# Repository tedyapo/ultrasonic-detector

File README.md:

# ultrasonic-detector
Digital down-converting ultrasonic detector

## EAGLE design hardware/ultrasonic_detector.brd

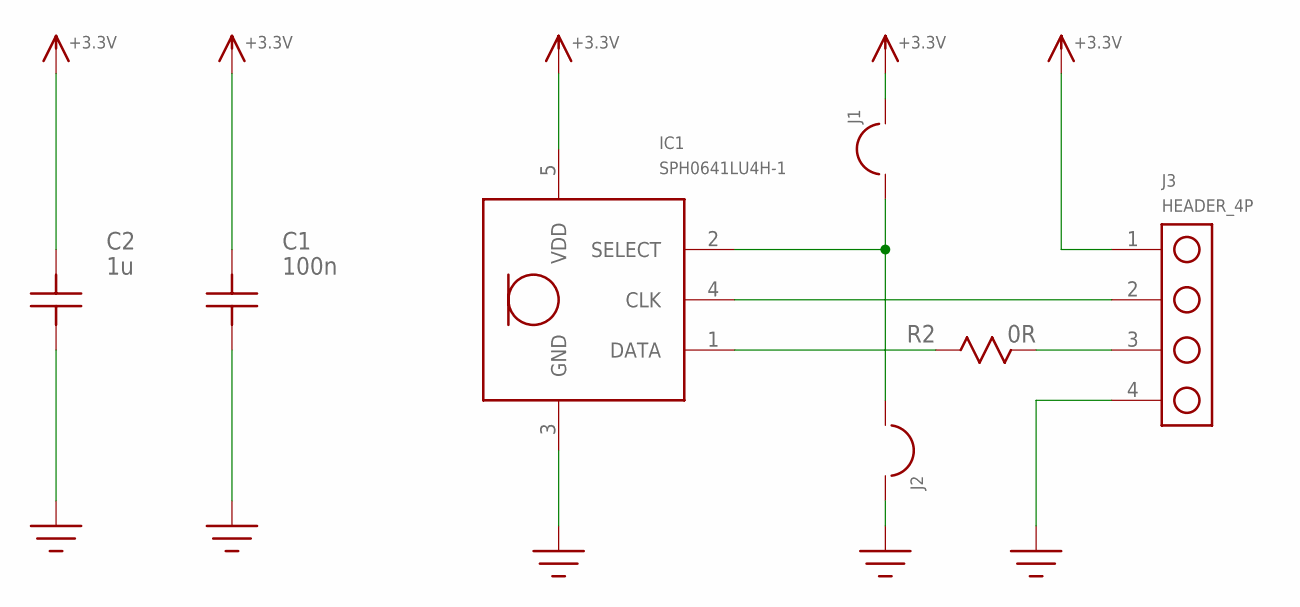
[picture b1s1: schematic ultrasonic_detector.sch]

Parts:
C1: 100n; C0603
C2: 1u; C0603
IC1: SPH0641LU4H-1
J1, J2: SOLDER_BRIDGE
J3: HEADER_4P
R2: 0R; R0603

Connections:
+3.3V: C1.P$2, C2.P$2, IC1.5 (VDD), J1.2@1, J1.2@2, J1.2@3, J3.1
GND: C1.P$1, C2.P$1, IC1.3 (GND), J2.2@1, J2.2@2, J2.2@3, J3.4
unnamed: IC1.2 (SELECT), J1.1, J2.1
unnamed: IC1.4 (CLK), J3.2
unnamed: IC1.1 (DATA), R2.P$1
unnamed: J3.3, R2.P$2

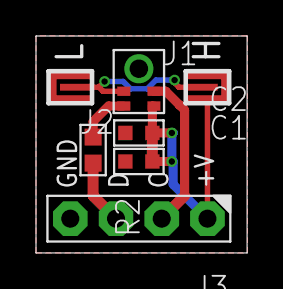
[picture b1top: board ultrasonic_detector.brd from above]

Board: 2 copper layers, 11.7 x 12.1 mm, 7 parts (0 on the bottom side), 6 nets.

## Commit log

2018-03-04 first PCB
